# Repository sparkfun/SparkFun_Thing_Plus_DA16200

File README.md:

SparkFun Thing Plus - DA16200
========================================

[*SparkFun Thing Plus - DA16200 (WRL-19696)*](https://www.sparkfun.com/products/19696)

The DA16200MOD is an ultra low power WiFi module manufactured by [Dialog (a subsidiary of Renesas)](https://www.renesas.com/us/en). It contains a 802.11b/g/n radio (PHY), a baseband processor, a media access controller (MAC), on-chip memory, and a host networking application processor, all on a single silicon die. The system on a chip (SoC) has full offload capabilities to run the entire networking OS and TCP/IP stack on chip; therefore, an external network processor, CPU, or microcontroller are not required.

The module is Wi-Fi Alliance certified for IEEE802.11b/g/n, Wi-Fi Direct, WPS functionalities and it has been approved by many countries including the United States (FCC), Canada (IC) and China (SRRC). Using the Wi-Fi Alliance transfer policy, the Wi-Fi Certifications can be transferred without being tested again. 

This module is now available in a [Thing Plus form factor](https://www.sparkfun.com/thing_plus), which includes a Qwiic and LiPo battery connectors, multiple GPIO pins, and JTAG PTH pins for debugging. The SparkFun Thing Plus - DA16200 is ideal for your next IoT project, thanks in part to the multiple sleep modes that allow you to take advantage of current draws as low as 0.2 - 3.5 &micro;A on the WiFi module.

***Note:** Please be aware that the Thing Plus - DA16200 has a **3.3V** logic level voltage.*

_The SparkFun [Qwiic connect system](https://www.sparkfun.com/qwiic) is an ecosystem of I2C sensors, actuators, shields and cables that make prototyping faster and less prone to error. All Qwiic-enabled boards use a common 1mm pitch, 4-pin JST connector. This reduces the amount of required PCB space, and polarized connections mean you can't hook it up wrong._

Repository Contents
-------------------

* **[/docs](/docs/)** - Documentation files
    * [board_files](/docs/board_files/) - Files for the product design
        * [Eagle design files](/docs/board_files/eagle_files.zip) (.zip)
        * [Schematic](/docs/board_files/schematic.pdf) (.pdf)
        * [Dimensions](/docs/board_files/dimensions.pdf) (.pdf)
    * [component_documentation](/docs/component_datasheets/) - Datasheets and guides for hardware components
    * [img/hookup_guide/](/docs/img/hookup_guide/) - Images for hookup guide documentation
* **[/Firmware](/Firmware/)** - Prebuilt Example Projects
* **/Hardware** - Eagle design files (.brd, .sch)
* **/Hardware/Production** - Production panel files (.brd)
* **Logic Analyzer Data** - Logic analyzer data from testing

Documentation
--------------

* [DA16200MOD Datasheet](https://www.renesas.com/document/dst/da16200mod-datasheet?language=en&r=1599971) (v3.1)
* [Hookup Guide](https://learn.sparkfun.com/tutorials/2517)
* [Getting Started with the DA16200 FreeRTOS SDK Tutorial](https://learn.sparkfun.com/tutorials/2418)
* [Dialog DA16200MOD Product Page](https://www.renesas.com/us/en/products/interface-connectivity/wireless-communications/wi-fi/da16200mod-ultra-low-power-wi-fi-modules-battery-powered-iot-devices)
  * [Documentation for the DA16200](https://www.renesas.com/us/en/products/interface-connectivity/wireless-communications/wi-fi/da16200mod-ultra-low-power-wi-fi-modules-battery-powered-iot-devices#document)       
  * [Software and Tools for the DA16200](https://www.renesas.com/us/en/products/interface-connectivity/wireless-communications/wi-fi/da16200mod-ultra-low-power-wi-fi-modules-battery-powered-iot-devices#design_development)
  * [Support for the DA16200](https://www.renesas.com/us/en/products/interface-connectivity/wireless-communications/wi-fi/da16200mod-ultra-low-power-wi-fi-modules-battery-powered-iot-devices#tools_support)
    * [RenesasRulz Forum](https://renesasrulz.com/)

Product Versions
----------------
* [WRL-19696](https://www.sparkfun.com/products/19696) -  initial release

License Information
-------------------

This product is _**open source**_! 

Please review the LICENSE.md file for license information. 

If you have any questions or concerns on licensing, please contact technical support on our [SparkFun forums](https://forum.sparkfun.com/index.php).

Distributed as-is; no warranty is given.

- Your friends at SparkFun.

_<COLLABORATION CREDIT>_

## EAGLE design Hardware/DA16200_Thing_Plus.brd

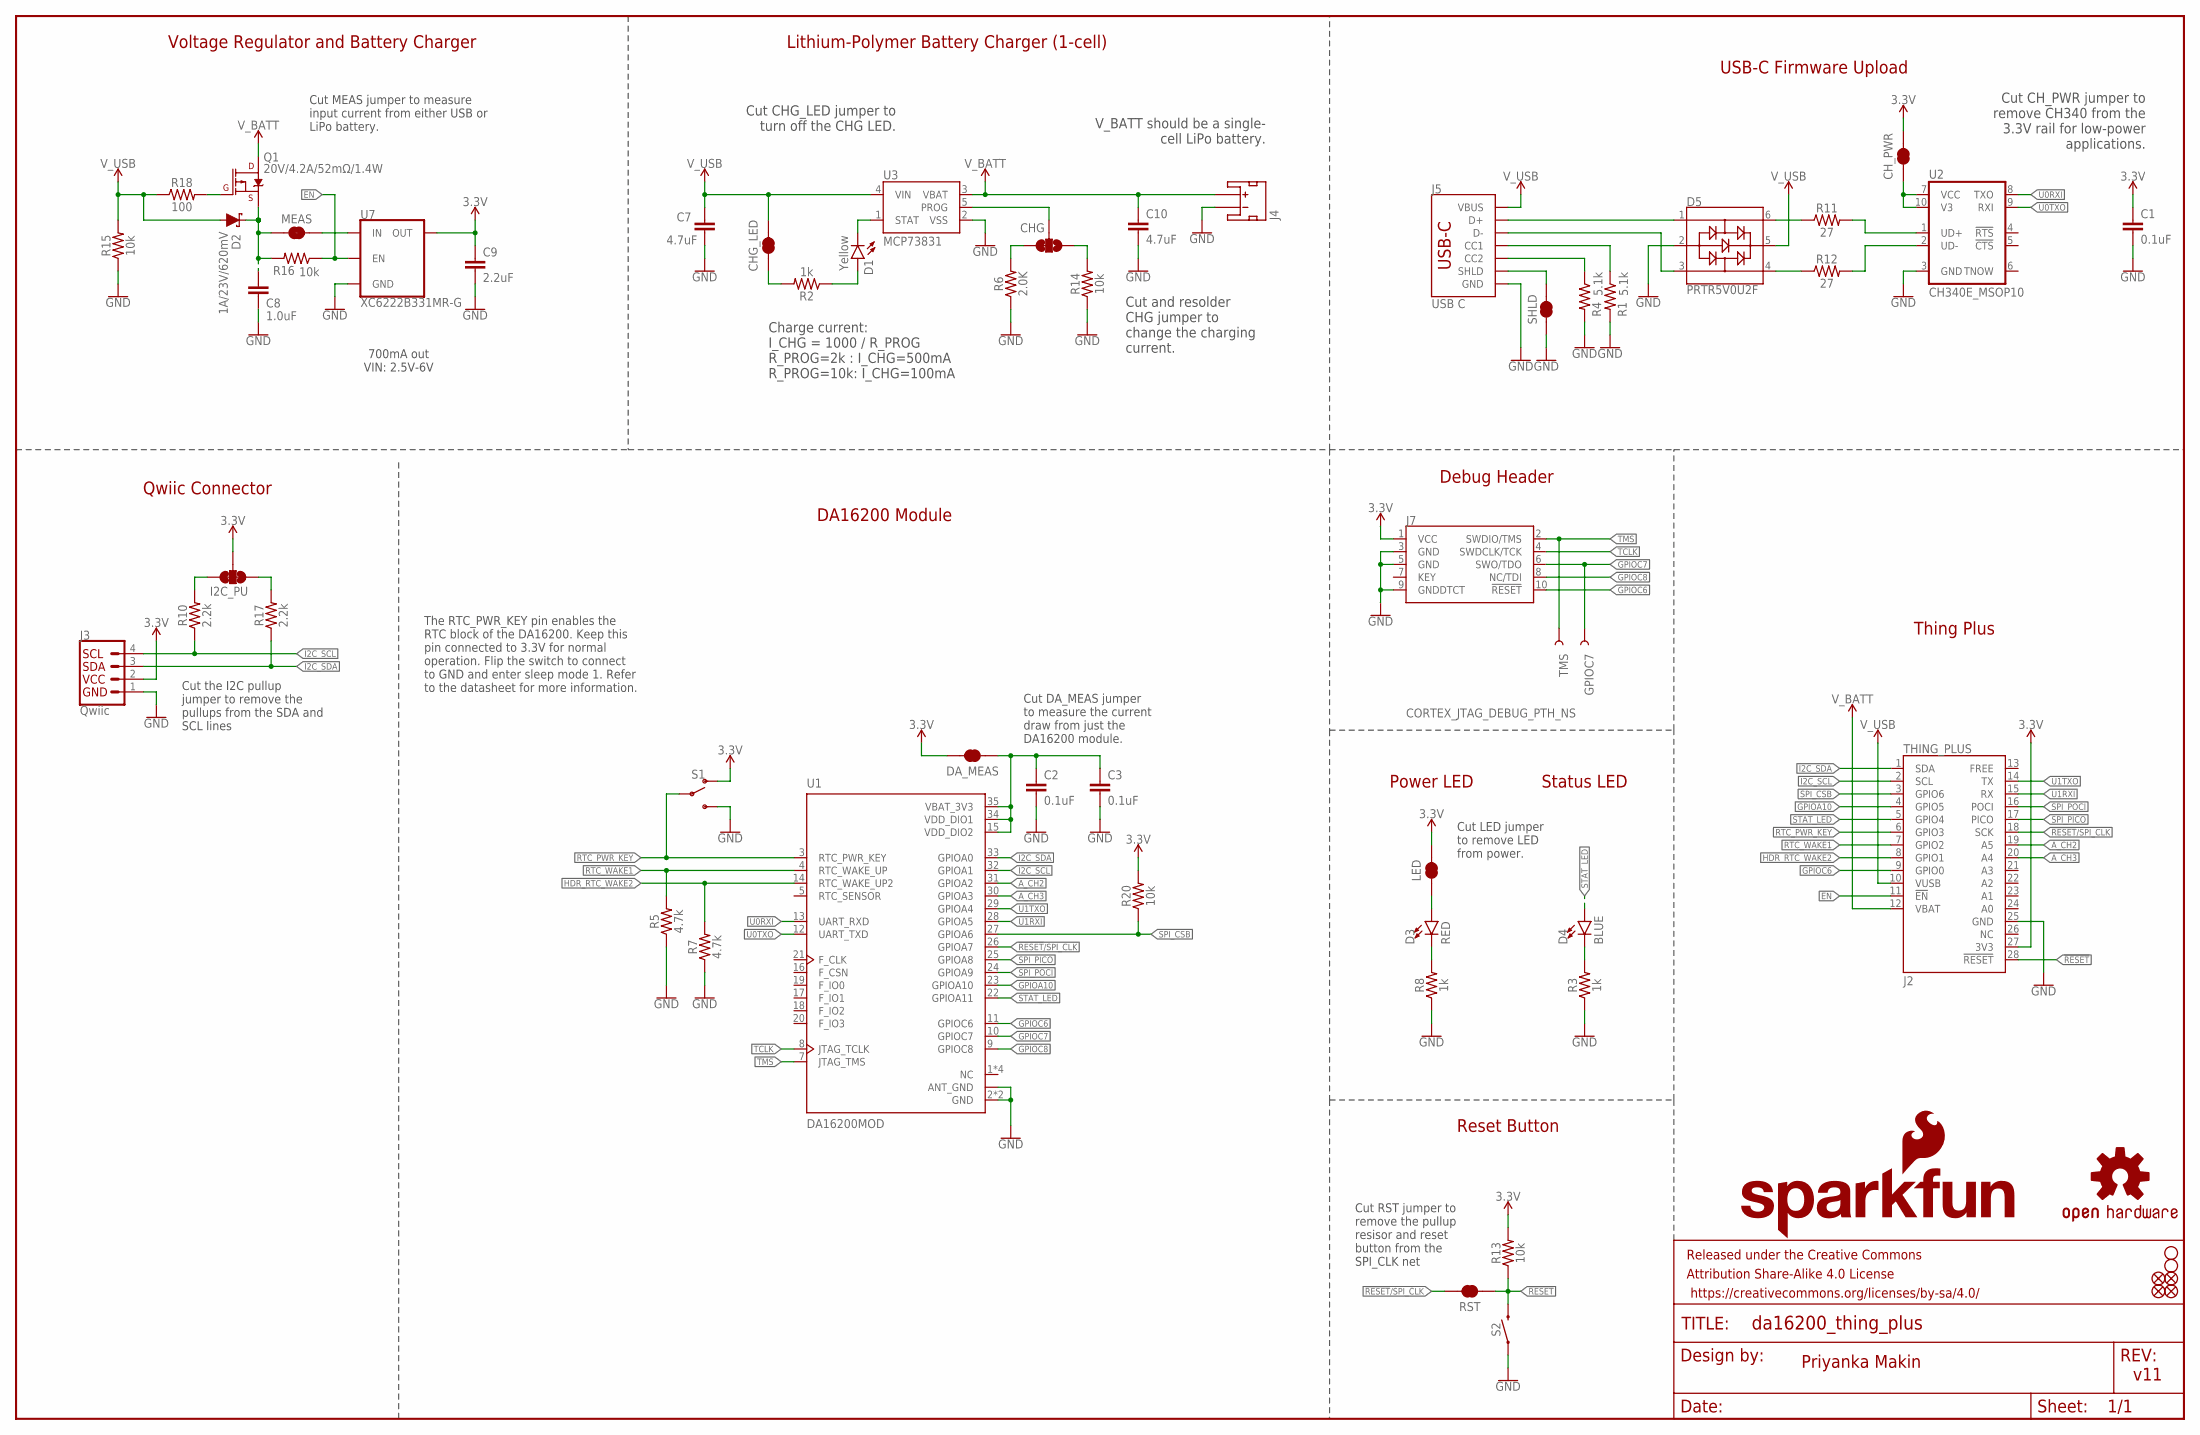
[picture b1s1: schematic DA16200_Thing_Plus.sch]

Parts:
C1, C2, C3: 0.1uF; 0402-TIGHT
C7, C10: 4.7uF; 0402-TIGHT
C8: 1.0uF; 0402-TIGHT
C9: 2.2uF; 0402-TIGHT
CHG: JUMPER-SMT_3_1-NC_TRACE_SILK; SMT-JUMPER_3_1-NC_TRACE_SILK
CHG_LED: JUMPER-SMT_2_NC_TRACE_SILK; SMT-JUMPER_2_NC_TRACE_SILK
CH_PWR: JUMPER-SMT_2_NC_TRACE_SILK; SMT-JUMPER_2_NC_TRACE_SILK
D1: Yellow; LED-0603
D2: 1A/23V/620mV; SOD-323
D3: RED; LED-0603
D4: BLUE; LED-0603
D5: PRTR5V0U2F; SOT886
DA_MEAS: JUMPER-SMT_2_NC_TRACE_SILK; SMT-JUMPER_2_NC_TRACE_SILK
FD1, FD2, FD3, FD4: FIDUCIALUFIDUCIAL; FIDUCIAL-MICRO
FRAME1: FRAME-LEDGER; CREATIVE_COMMONS
GPIOC7: TEST-POINT3; PAD.03X.03
H3, H4: STAND-OFF
I2C_PU: JUMPER-SMT_3_2-NC_TRACE_SILK; SMT-JUMPER_3_2-NC_TRACE_SILK
J2: THING_PLUS
J3: Qwiic; JST04_1MM_RA
J4: JST_2MM_MALE; JST-2-SMD
J5: USB C; USB-C-16P-4LAYER-ISOLATED
J7: CORTEX_JTAG_DEBUG_PTH_NS; 2X5-PTH-1.27MM-NO_SILK
LED: JUMPER-SMT_2_NC_TRACE_SILK; SMT-JUMPER_2_NC_TRACE_SILK
LOGO1: OSHW-LOGOS; OSHW-LOGO-S
LOGO2: SFE_LOGO_NAME_FLAME.1_INCH; SFE_LOGO_NAME_FLAME_.1
MEAS: JUMPER-COMBO_2_NC_TRACE; COMBO-JUMPER_2_NC_TRACE
Q1: 20V/4.2A/52mΩ/1.4W; SOT23-3
R1, R4: 5.1k; 0402-TIGHT
R2, R3, R8: 1k; 0402-TIGHT
R5, R7: 4.7k; 0402-TIGHT
R6: 2.0K; 0402-TIGHT
R10, R17: 2.2k; 0402-TIGHT
R11, R12: 27; 0402-TIGHT
R13, R14, R15, R16, R20: 10k; 0402-TIGHT
R18: 100; 0402-TIGHT
RST: JUMPER-SMT_2_NC_TRACE_SILK; SMT-JUMPER_2_NC_TRACE_SILK
S1: SWITCH-SPDT-SMD-AYZ0202; SWITCH_DPDT_SMD_AYZ0202
S2: MOMENTARY-SWITCH-SPST-SMD-5.2MM-TALL; TACTILE_SWITCH_SMD_5.2MM
SHLD: JUMPER-SMT_2_NC_TRACE_SILK; SMT-JUMPER_2_NC_TRACE_SILK
TMS: TEST-POINT3; PAD.03X.03
U1: DA16200MOD; XCVR_DA16200MOD-AAC4WA32
U2: CH340E_MSOP10; MSOP10
U3: MCP73831; SOT23-5
U7: XC6222B331MR-G; SOT23-5

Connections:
3.3V: C1.1, C9.1, CH_PWR.2, DA_MEAS.2, I2C_PU.2, J2.27 (3V3), J3.2, J7.1 (VCC), LED.2, R13.2, R20.2, S1.1 (O), U7.5 (OUT)
!RESET!: J2.28 (!RESET), R13.1, RST.1, S2.3 (2)
!RESET!/SPI_CLK: J2.18 (SCK), RST.2, U1.26 (GPIOA7)
A_CH2: J2.19 (A5), U1.31 (GPIOA2)
A_CH3: J2.20 (A4), U1.30 (GPIOA3)
EN: J2.11 (!EN), R16.1, U7.3 (EN)
GND: C1.2, C2.2, C3.2, C7.2, C8.2, C9.2, C10.2, D5.2, J2.25 (GND), J3.1, J4.1 (-), J5.GND, J5.GND2 (GND), J7.3 (GND), J7.5 (GND), J7.9 (GNDDTCT), R1.2, R3.1, R4.2, R5.1, R6.1, R7.1, R8.1, R14.1, R15.1, S1.3 (S), S2.1, SHLD.1, U1.2 (GND), U1.ANT_GND, U1.GND, U2.3 (GND), U3.2 (VSS), U7.2 (GND)
GPIOA10: J2.4 (GPIO5), U1.23 (GPIOA10)
GPIOC6: J2.9 (GPIO0), J7.10 (!RESET), U1.11 (GPIOC6)
GPIOC7: GPIOC7.1, J7.6 (SWO/TDO), U1.10 (GPIOC7)
GPIOC8: J7.8 (NC/TDI), U1.9 (GPIOC8)
HDR_RTC_WAKE2: J2.8 (GPIO1), R7.2, U1.14 (RTC_WAKE_UP2)
I2C_SCL: J2.2 (SCL), J3.4, R10.1, U1.32 (GPIOA1)
I2C_SDA: J2.1 (SDA), J3.3, R17.1, U1.33 (GPIOA0)
unnamed: D4.C, R3.2
unnamed: I2C_PU.3, R10.2
unnamed: I2C_PU.1, R17.2
unnamed: D3.A, LED.1
unnamed: D5.1, J5.A6 (D+), J5.B6 (D+)
unnamed: D5.3, J5.A7 (D-), J5.B7 (D-)
unnamed: D3.C, R8.2
unnamed: C2.1, C3.1, DA_MEAS.1, U1.15 (VDD_DIO2), U1.34 (VDD_DIO1), U1.35 (VBAT_3V3)
unnamed: D1.C, U3.1 (STAT)
unnamed: CHG.3, R6.2
unnamed: J5.A5 (CC1), R1.1
unnamed: J5.B5 (CC2), R4.1
unnamed: D5.6, R11.1
unnamed: CHG.2, U3.5 (PROG)
unnamed: C8.1, D2.C, MEAS.1, MEAS.3 (1), Q1.2 (S), R16.2
unnamed: D5.4, R12.1
unnamed: D1.A, R2.1
unnamed: R11.2, U2.1 (UD+)
unnamed: R12.2, U2.2 (UD-)
unnamed: CHG.1, R14.2
unnamed: Q1.1 (G), R18.2
unnamed: MEAS.2, MEAS.4 (2), U7.1 (IN)
unnamed: CHG_LED.1, R2.2
unnamed: J5.SHLD1 (SHLD), J5.SHLD2 (SHLD), J5.SHLD3 (SHLD), J5.SHLD4 (SHLD), J5.SHLD5 (SHLD), J5.SHLD6 (SHLD), J5.SHLD7 (SHLD), J5.SHLD8 (SHLD), SHLD.2
unnamed: CH_PWR.1, U2.7 (VCC), U2.10 (V3)
RTC_PWR_KEY: J2.6 (GPIO3), S1.2, U1.3 (RTC_PWR_KEY)
RTC_WAKE1: J2.7 (GPIO2), R5.2, U1.4 (RTC_WAKE_UP)
SPI_CSB: J2.3 (GPIO6), R20.1, U1.27 (GPIOA6)
SPI_PICO: J2.17 (PICO), U1.25 (GPIOA8)
SPI_POCI: J2.16 (POCI), U1.24 (GPIOA9)
STAT_LED: D4.A, J2.5 (GPIO4), U1.22 (GPIOA11)
TCLK: J7.4 (SWDCLK/TCK), U1.8 (JTAG_TCLK)
TMS: J7.2 (SWDIO/TMS), TMS.1, U1.7 (JTAG_TMS)
U0RXI: U1.13 (UART_RXD), U2.8 (TXO)
U0TXO: U1.12 (UART_TXD), U2.9 (RXI)
U1RXI: J2.15 (RX), U1.28 (GPIOA5)
U1TXO: J2.14 (TX), U1.29 (GPIOA4)
V_BATT: C10.1, J2.12 (VBAT), J4.2 (+), Q1.3 (D), U3.3 (VBAT)
V_USB: C7.1, CHG_LED.2, D2.A, D5.5, J2.10 (VUSB), J5.VBUS1 (VBUS), J5.VBUS2 (VBUS), R15.2, R18.1, U3.4 (VIN)

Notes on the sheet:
V_BATT should be a single- cell LiPo battery.
Charge current: I_CHG = 1000 / R_PROG R_PROG=2k : I_CHG=500mA R_PROG=10k: I_CHG=100mA
Voltage Regulator and Battery Charger
Lithium-Polymer Battery Charger (1-cell)
700mA out VIN: 2.5V-6V
Reset Button
Status LED
Thing Plus
v11
Qwiic Connector
USB-C Firmware Upload
Cut the I2C pullup jumper to remove the pullups from the SDA and SCL lines
Debug Header
Power LED
Priyanka Makin
DA16200 Module
Cut MEAS jumper to measure input current from either USB or LiPo battery.
Cut and resolder CHG jumper to change the charging current.
Cut LED jumper to remove LED from power.
The RTC_PWR_KEY pin enables the RTC block of the DA16200. Keep this pin connected to 3.3V for normal operation. Flip the switch to connect to GND and enter sleep mode 1. Refer to the datasheet for more information.
Cut DA_MEAS jumper to measure the current draw from just the DA16200 module.
Cut CHG_LED jumper to turn off the CHG LED.
Cut CH_PWR jumper to remove CH340 from the 3.3V rail for low-power applications.
Cut RST jumper to remove the pullup resisor and reset button from the SPI_CLK net

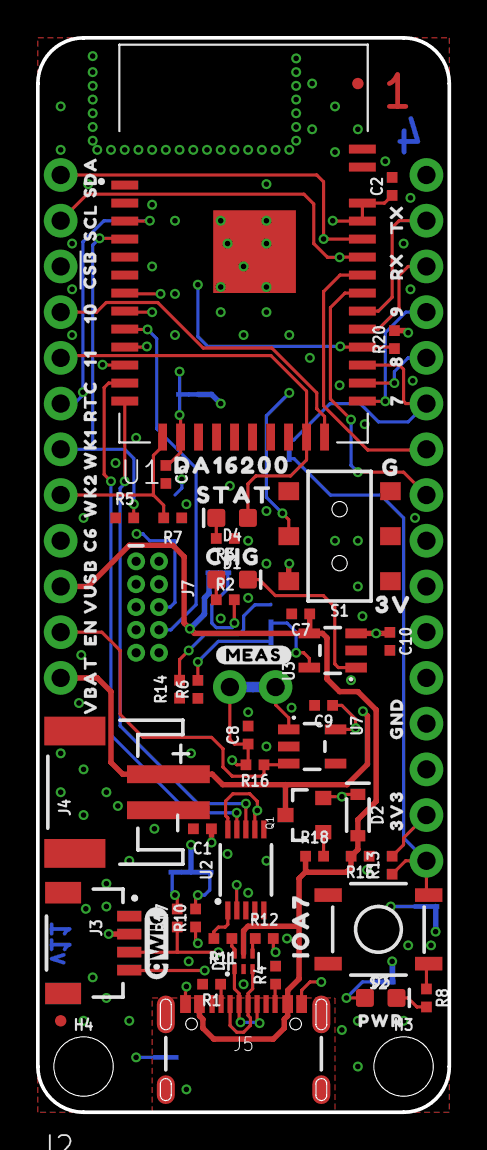
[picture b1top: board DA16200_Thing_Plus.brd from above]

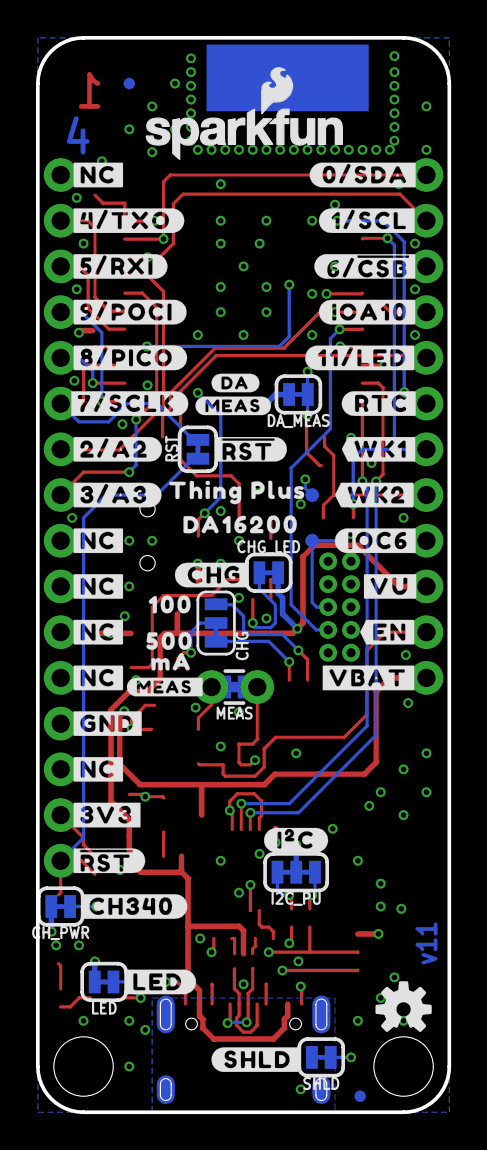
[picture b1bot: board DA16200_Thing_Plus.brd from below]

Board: 4 copper layers, 22.9 x 59.7 mm, 133 parts (57 on the bottom side), 53 nets.

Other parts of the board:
U$1: STAT0
U$2: CHG0
U$3: #MEAS_#0
U$4: G0
U$5, U$43: ##RST##0
U$6: #VU#0
U$7: #IOA10#0
U$8, U$29: #MEAS#0
U$9: 3V0
U$10: #CH340#0
U$11: #0#SDA#0
U$12: #1#SCL#0
U$13: IOA7_0
U$14, U$15, U$18, U$19, U$20, U$40: #NC#0
U$16: PWR0
U$17: #DA#0
U$21: 5000
U$22: 1000
U$23: MA0
U$24: SDA0
U$25: SCL0
U$26: #CSB#0
U$27: #4#TXO#0
U$28: 110
U$30: #VBAT#0
U$31: ORDERING_INSTRUCTIONS
U$32: 100
U$33: RTC0
U$34: WK10
U$35: WK20
U$36: #5#RXI#0
U$37: EN0
U$38: VUSB0
U$39: VBAT0
U$41: TX0
U$42: RX0
U$44: 90
U$45: 80
U$47: 70
U$50: #GND#0
U$51: #3V3#0
U$53: #EN#0
U$55: GND0
U$56: THING_PLUS0
U$57: 3V30
U$59: #CHG#0
U$60: #IOC6#0
U$62: #6##CSB##0
U$63: #11#LED#0
U$64: QWIIC_4MM
U$65: C60
U$66: #9#POCI#0
U$67: #8#PICO#0
U$68: #7#SCLK#0
U$69: #2#A2#0
U$70: #3#A3#0
U$71: #WK2#0
U$72: #WK1#0
U$73: #RTC#0
U$80, U$81: DA162000
U$82: #I�C#0
U$84: #LED#0
U$85: #SHLD#0

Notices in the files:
parts and their libraries:
SparkFun-Resistors: Licensing: Creative Commons ShareAlike 4.0 International - https://creativecommons.org/licenses/by-sa/4.0
SparkFun-Aesthetics: Released under the Creative Commons Attribution Share-Alike 4.0 License
SparkFun-Aesthetics: https://creativecommons.org/licenses/by-sa/4.0
